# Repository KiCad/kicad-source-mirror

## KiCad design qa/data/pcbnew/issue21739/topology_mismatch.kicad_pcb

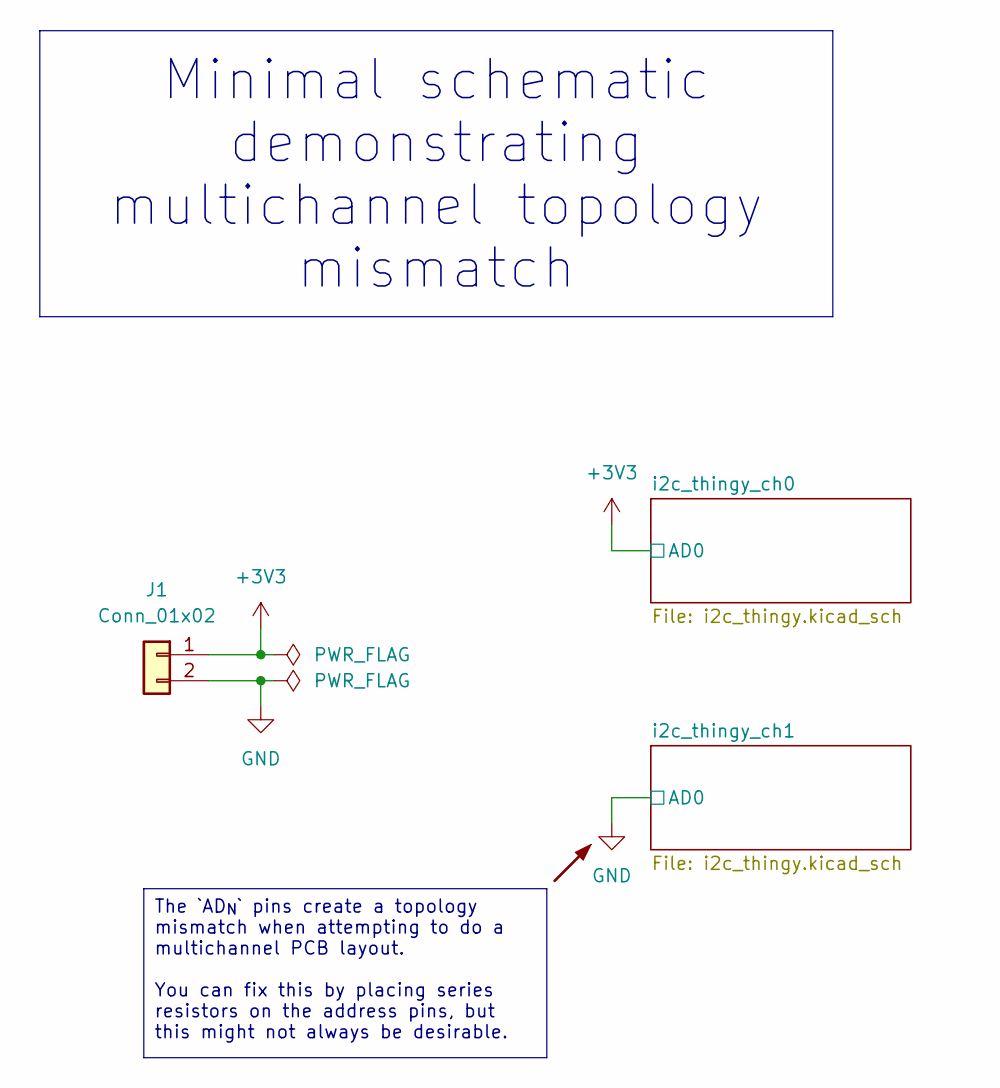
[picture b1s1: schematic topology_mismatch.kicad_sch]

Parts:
J1: Conn_01x02; PinHeader_1x02_P2.54mm_Vertical

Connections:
+3V3: J1.1; also elsewhere on the board
GND: J1.2; also elsewhere on the board

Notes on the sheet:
Minimal schematic demonstrating multichannel topology mismatch
The `AD_{N}` pins create a topology mismatch when attempting to do a multichannel PCB layout. You can fix this by placing series resistors on the address pins, but this might not always be desirable.

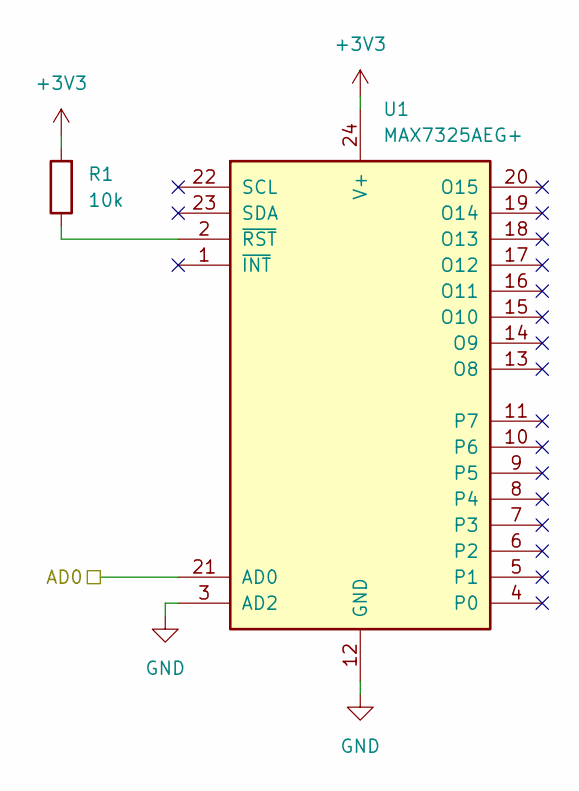
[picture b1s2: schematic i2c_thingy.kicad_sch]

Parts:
R1: 10k; R_0603_1608Metric
U1: MAX7325AEG+; QSOP-24_3.9x8.7mm_P0.635mm

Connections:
+3V3: R1.2, U1.21 (AD0), U1.24 (V+); also elsewhere on the board
GND: U1.3 (AD2), U1.12 (GND); also elsewhere on the board
unnamed: R1.1, U1.2 (~RST)

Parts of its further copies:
R2: 10k; R_0603_1608Metric
U2: MAX7325AEG+; QSOP-24_3.9x8.7mm_P0.635mm

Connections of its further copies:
+3V3: R2.2, U2.24 (V+); also elsewhere on the board
GND: U2.3 (AD2), U2.12 (GND), U2.21 (AD0); also elsewhere on the board
unnamed: R2.1, U2.2 (~RST)

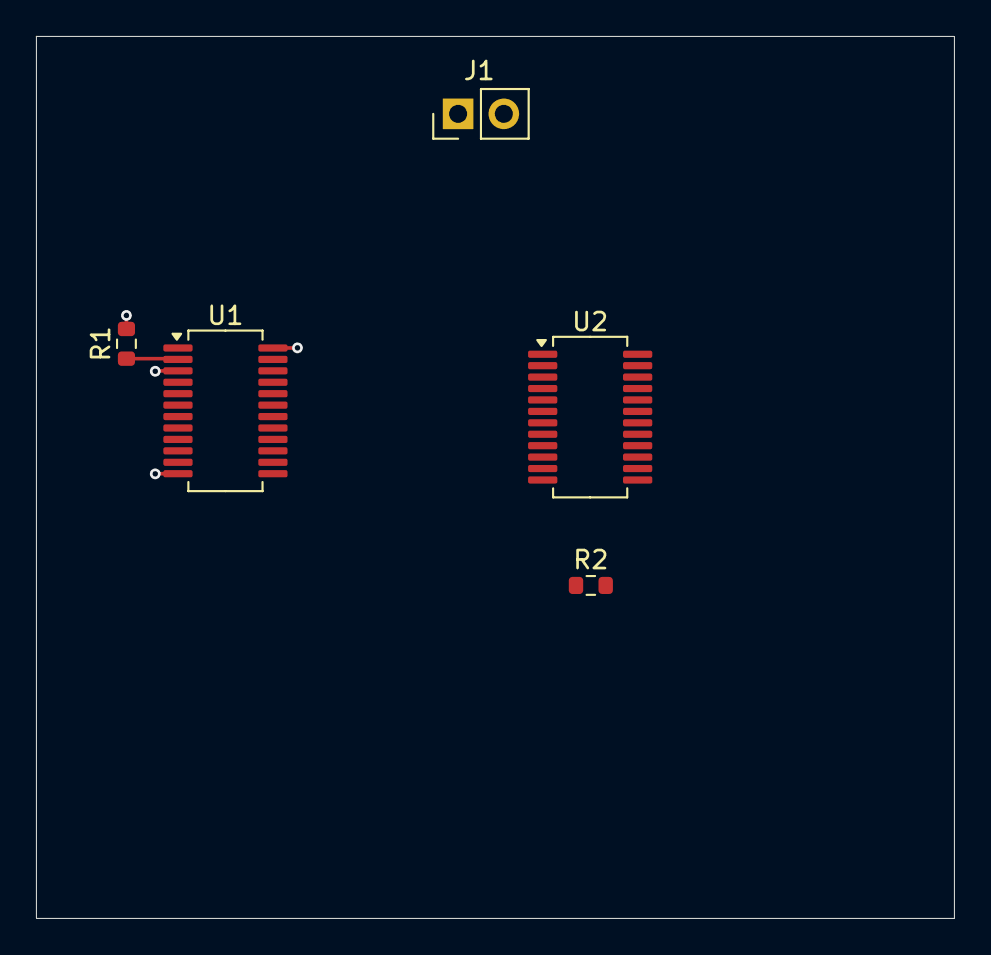
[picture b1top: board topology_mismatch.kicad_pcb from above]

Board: 4 copper layers, 51.0 x 49.0 mm, 5 parts (0 on the bottom side), 4 nets.

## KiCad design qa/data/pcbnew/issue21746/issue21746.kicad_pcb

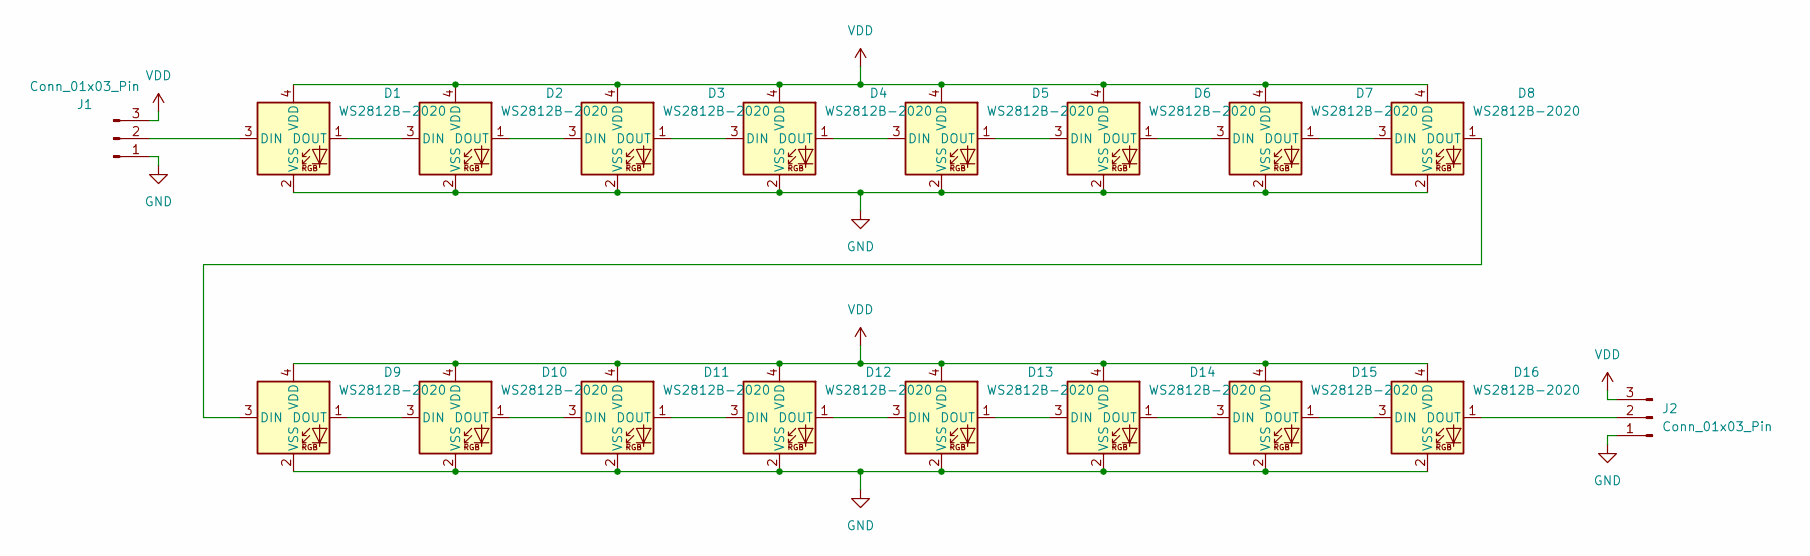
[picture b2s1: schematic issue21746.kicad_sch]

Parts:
D1, D2, D3, D4, D5, D6, D7, D8, D9, D10, D11, D12, D13, D14, D15, D16: WS2812B-2020; LED_WS2812B-2020_PLCC4_2.0x2.0mm
J1, J2: Conn_01x03_Pin; PinHeader_1x03_P2.54mm_Vertical

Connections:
GND: D1.2 (VSS), D2.2 (VSS), D3.2 (VSS), D4.2 (VSS), D5.2 (VSS), D6.2 (VSS), D7.2 (VSS), D8.2 (VSS), D9.2 (VSS), D10.2 (VSS), D11.2 (VSS), D12.2 (VSS), D13.2 (VSS), D14.2 (VSS), D15.2 (VSS), D16.2 (VSS), J1.1, J2.1
unnamed: D1.3 (DIN), J1.2
unnamed: D1.1 (DOUT), D2.3 (DIN)
unnamed: D2.1 (DOUT), D3.3 (DIN)
unnamed: D3.1 (DOUT), D4.3 (DIN)
unnamed: D4.1 (DOUT), D5.3 (DIN)
unnamed: D5.1 (DOUT), D6.3 (DIN)
unnamed: D6.1 (DOUT), D7.3 (DIN)
unnamed: D7.1 (DOUT), D8.3 (DIN)
unnamed: D8.1 (DOUT), D9.3 (DIN)
unnamed: D9.1 (DOUT), D10.3 (DIN)
unnamed: D10.1 (DOUT), D11.3 (DIN)
unnamed: D11.1 (DOUT), D12.3 (DIN)
unnamed: D12.1 (DOUT), D13.3 (DIN)
unnamed: D13.1 (DOUT), D14.3 (DIN)
unnamed: D14.1 (DOUT), D15.3 (DIN)
unnamed: D15.1 (DOUT), D16.3 (DIN)
unnamed: D16.1 (DOUT), J2.2
VDD: D1.4 (VDD), D2.4 (VDD), D3.4 (VDD), D4.4 (VDD), D5.4 (VDD), D6.4 (VDD), D7.4 (VDD), D8.4 (VDD), D9.4 (VDD), D10.4 (VDD), D11.4 (VDD), D12.4 (VDD), D13.4 (VDD), D14.4 (VDD), D15.4 (VDD), D16.4 (VDD), J1.3, J2.3

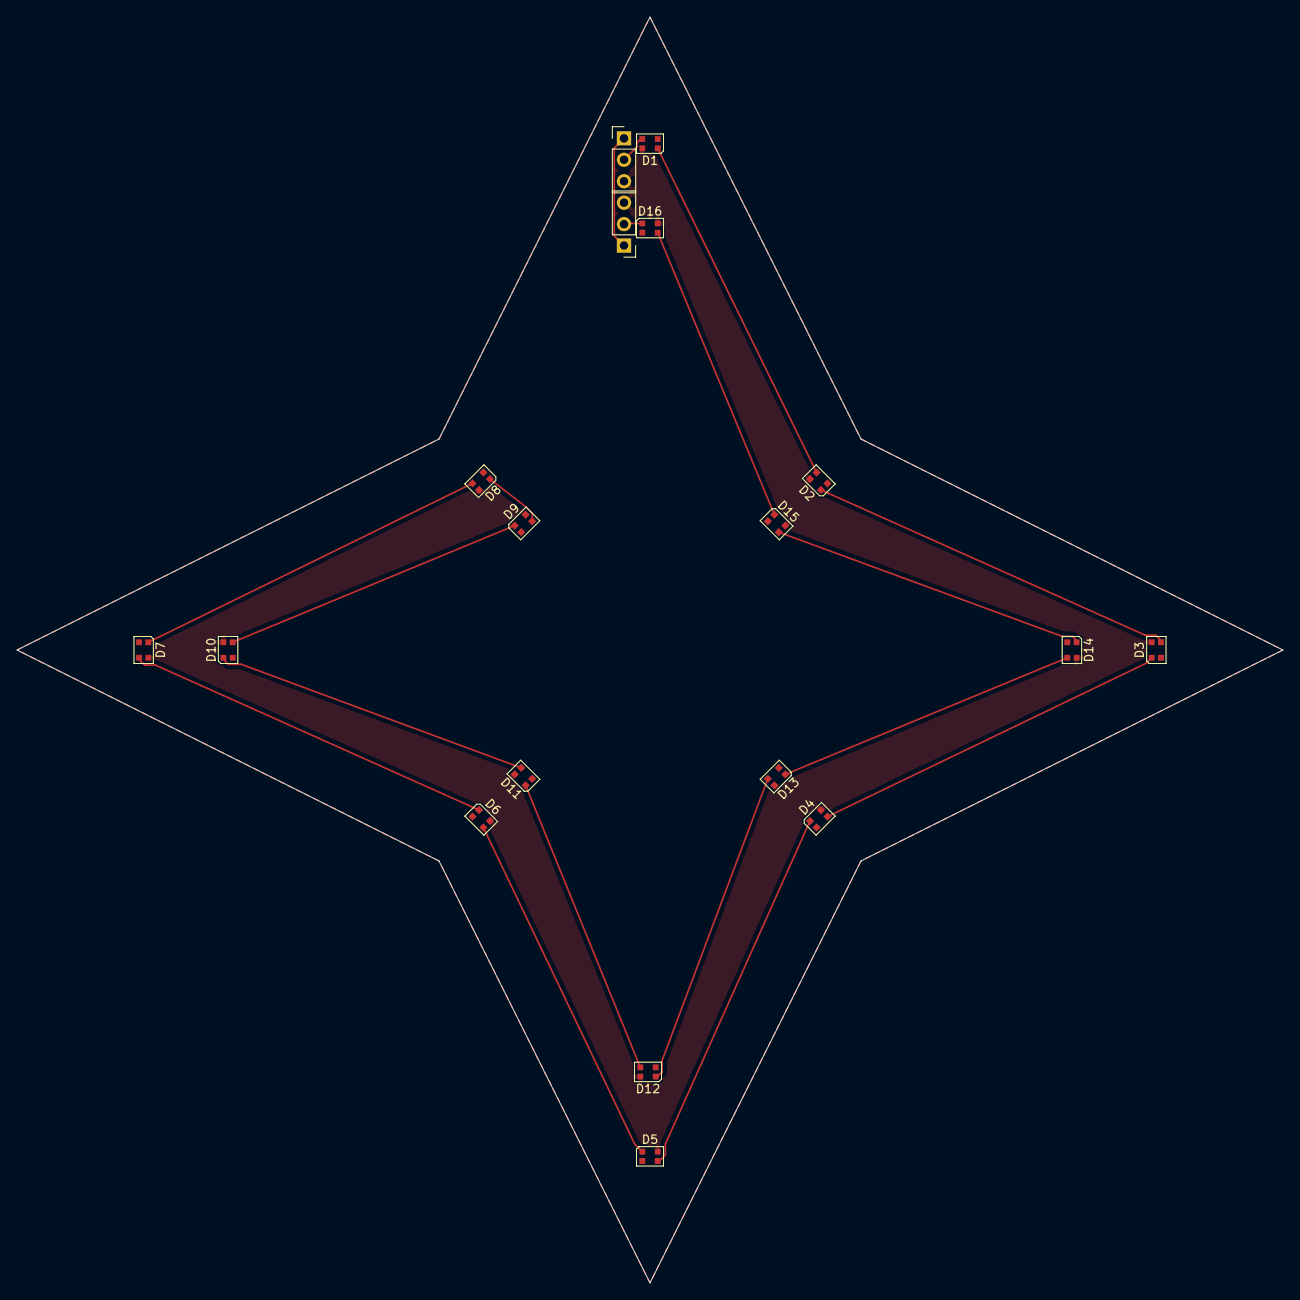
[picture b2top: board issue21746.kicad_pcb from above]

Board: 2 copper layers, 150.0 x 150.0 mm, 18 parts (0 on the bottom side), 19 nets.

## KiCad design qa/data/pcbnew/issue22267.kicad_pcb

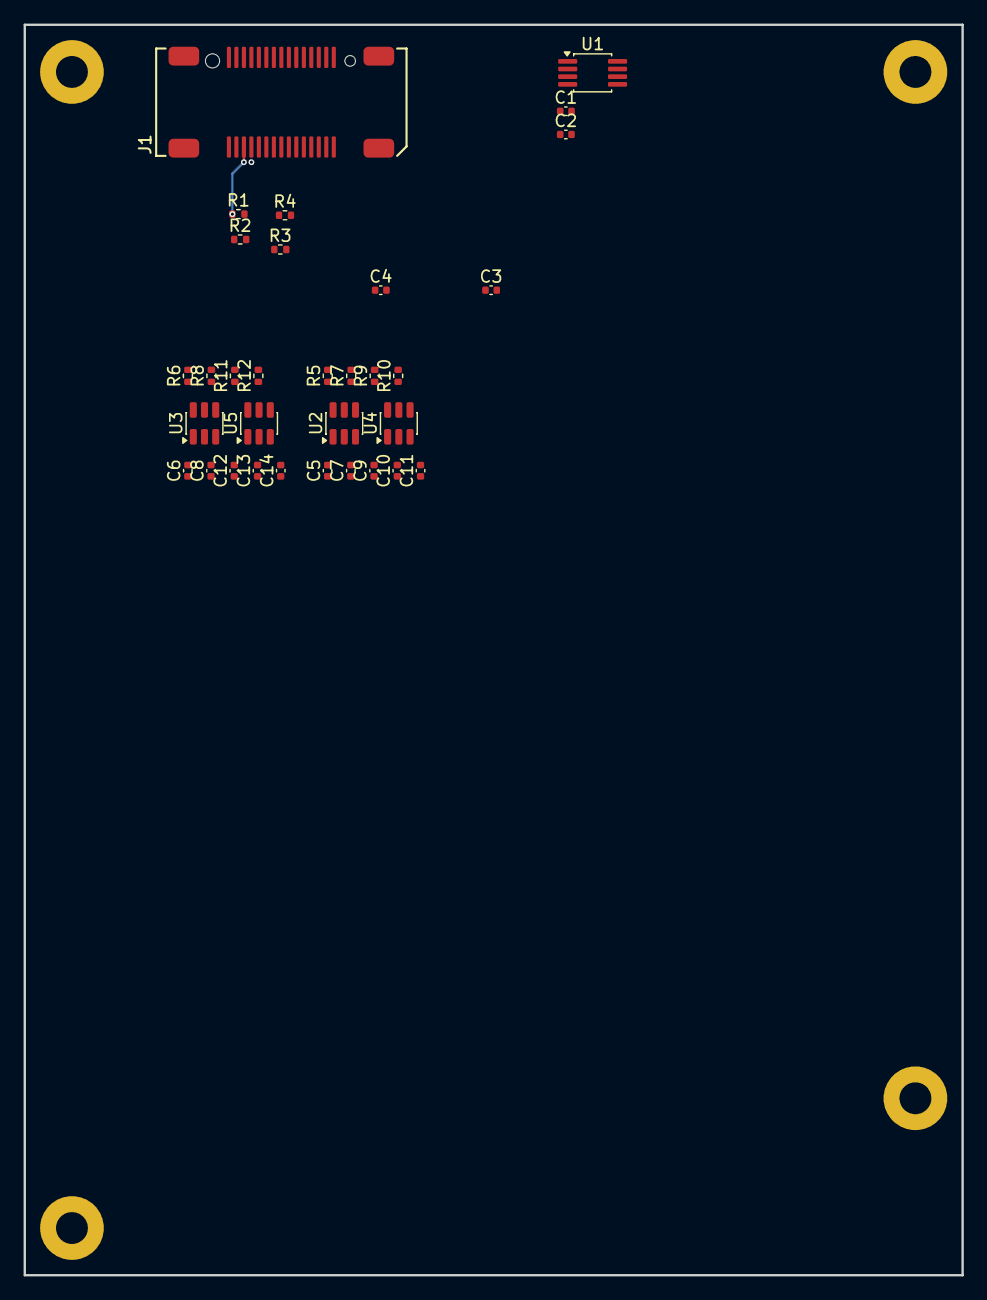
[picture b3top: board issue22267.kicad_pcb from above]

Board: 4 copper layers, 79.5 x 106.0 mm, 32 parts (0 on the bottom side), 16 nets.

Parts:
C1, C2, C3, C4, C5, C6, C10, C11, C13, C14: 2.2uF 25V; C_0402_1005Metric
C7, C8, C9, C12: tbd; C_0402_1005Metric
J1: MA01F030VABB
R1, R2, R3, R4: tbd(100?); R_0402_1005Metric
R5, R6, R7, R8, R9, R10, R11, R12: tbd; R_0402_1005Metric
U1: MSOP-8_3x3mm_P0.65mm
U2, U3, U4, U5: SOT-23-6

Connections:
GND: C1.2, C2.2, C3.2, C4.2, C5.2, C6.2, C10.2, C11.2, C13.2, C14.2, J1.1, J1.2, J1.5, J1.8, J1.11, J1.14, J1.15, J1.19, J1.22, J1.25, J1.26, J1.28, J1.30, R1.2, R2.2, R3.2, R4.2, R5.2, R6.2, R9.2, R11.2, U1.4 (GND)
unnamed: C7.2, R7.1, U2.1
unnamed: C8.2, R8.1, U3.1
unnamed: C9.2, R10.1, U4.1
unnamed: C12.2, R12.1, U5.1
unnamed: C7.1, R5.1, R7.2, U2.4 (-)
unnamed: C8.1, R6.1, R8.2, U3.4 (-)
unnamed: C9.1, R9.1, R10.2, U4.4 (-)
unnamed: C12.1, R11.1, R12.2, U5.4 (-)
SIG0A: J1.13, R1.1, U2.3 (+)
SIG0B: J1.12, R2.1, U4.3 (+)
SIG1A: J1.10, R3.1, U3.3 (+)
SIG1B: J1.9, R4.1, U5.3 (+)
VM1R5: C5.1, C6.1, C11.1, C14.1, U2.2 (V-), U3.2 (V-), U4.2 (V-), U5.2 (V-)
VP3R3A: C1.1, C3.1, C4.1, C10.1, C13.1, J1.20, U1.2 (V_{IN}), U2.5 (~DISABLE), U2.6 (V+), U3.5 (~DISABLE), U3.6 (V+), U4.5 (~DISABLE), U4.6 (V+), U5.5 (~DISABLE), U5.6 (V+)
VREF2P5: C2.1, U1.6 (V_{OUT})

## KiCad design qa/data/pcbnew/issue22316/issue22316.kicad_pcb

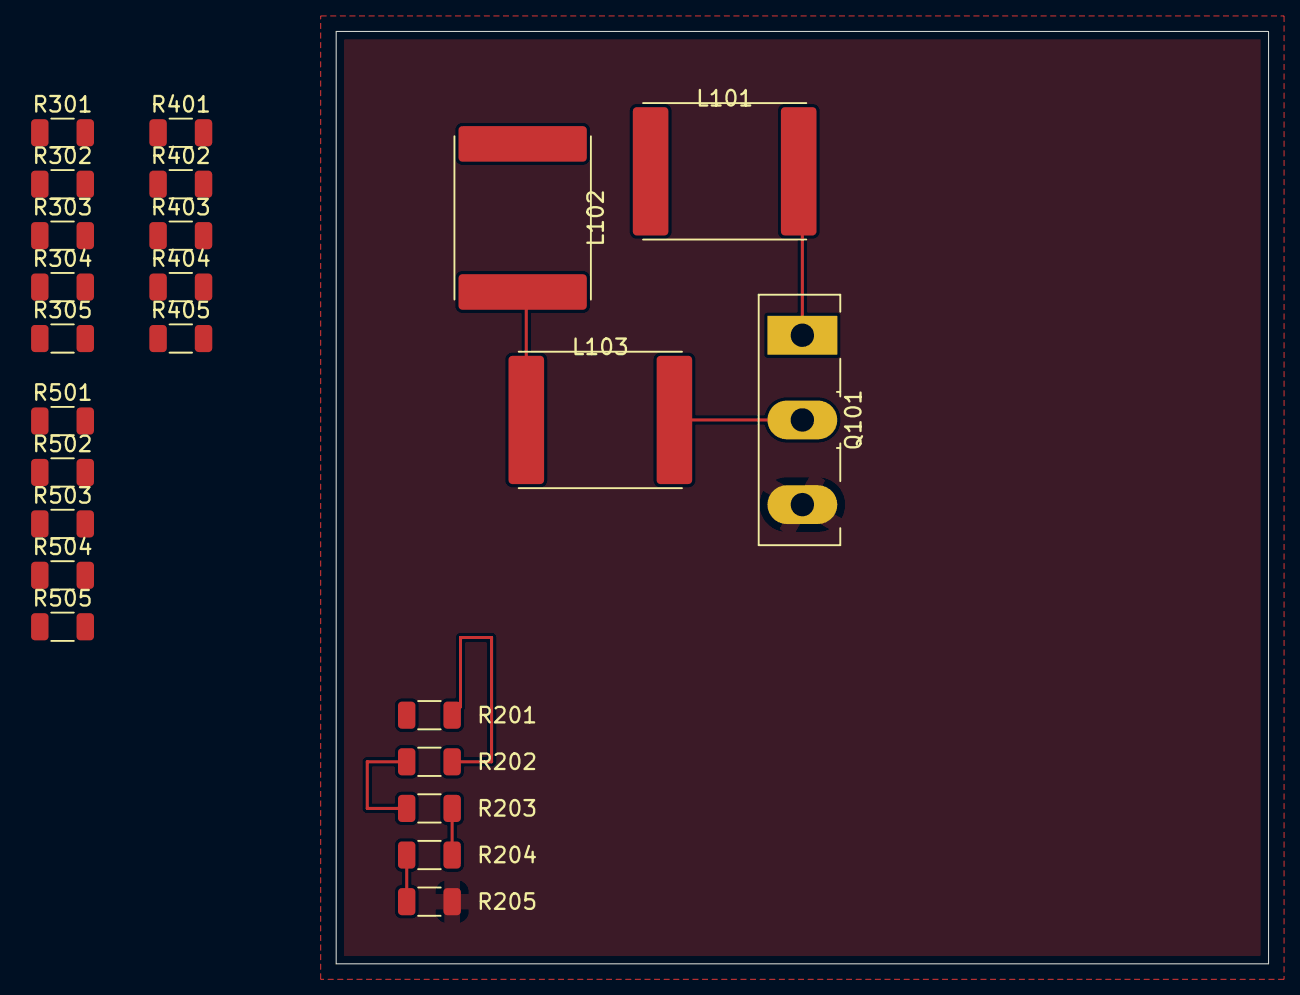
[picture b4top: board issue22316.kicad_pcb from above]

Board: 2 copper layers, 60.0 x 60.0 mm, 24 parts (0 on the bottom side), 21 nets.

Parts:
L101, L102, L103: L; L_Coilcraft_2929SQ-331
Q101: Q_NMOS_GDS; TO-247-3_Vertical
R201, R202, R203, R204, R205, R301, R302, R303, R304, R305, R401, R402, R403, R404, R405, R501, R502, R503, R504, R505: R; R_1206_3216Metric

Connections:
+24V: R201.1, R301.1, R401.1, R501.1
GND: Q101.3 (S), R205.2, R305.2, R405.2, R505.2
unnamed: L102.2, L103.1
unnamed: L103.2, Q101.2 (D)
unnamed: L101.2, Q101.1 (G)
unnamed: R201.2, R202.2
unnamed: R202.1, R203.1
unnamed: R203.2, R204.2
unnamed: R204.1, R205.1
unnamed: R301.2, R302.2
unnamed: R302.1, R303.1
unnamed: R303.2, R304.2
unnamed: R304.1, R305.1
unnamed: R401.2, R402.2
unnamed: R402.1, R403.1
unnamed: R403.2, R404.2
unnamed: R404.1, R405.1
unnamed: R501.2, R502.2
unnamed: R502.1, R503.1
unnamed: R503.2, R504.2
unnamed: R504.1, R505.1
